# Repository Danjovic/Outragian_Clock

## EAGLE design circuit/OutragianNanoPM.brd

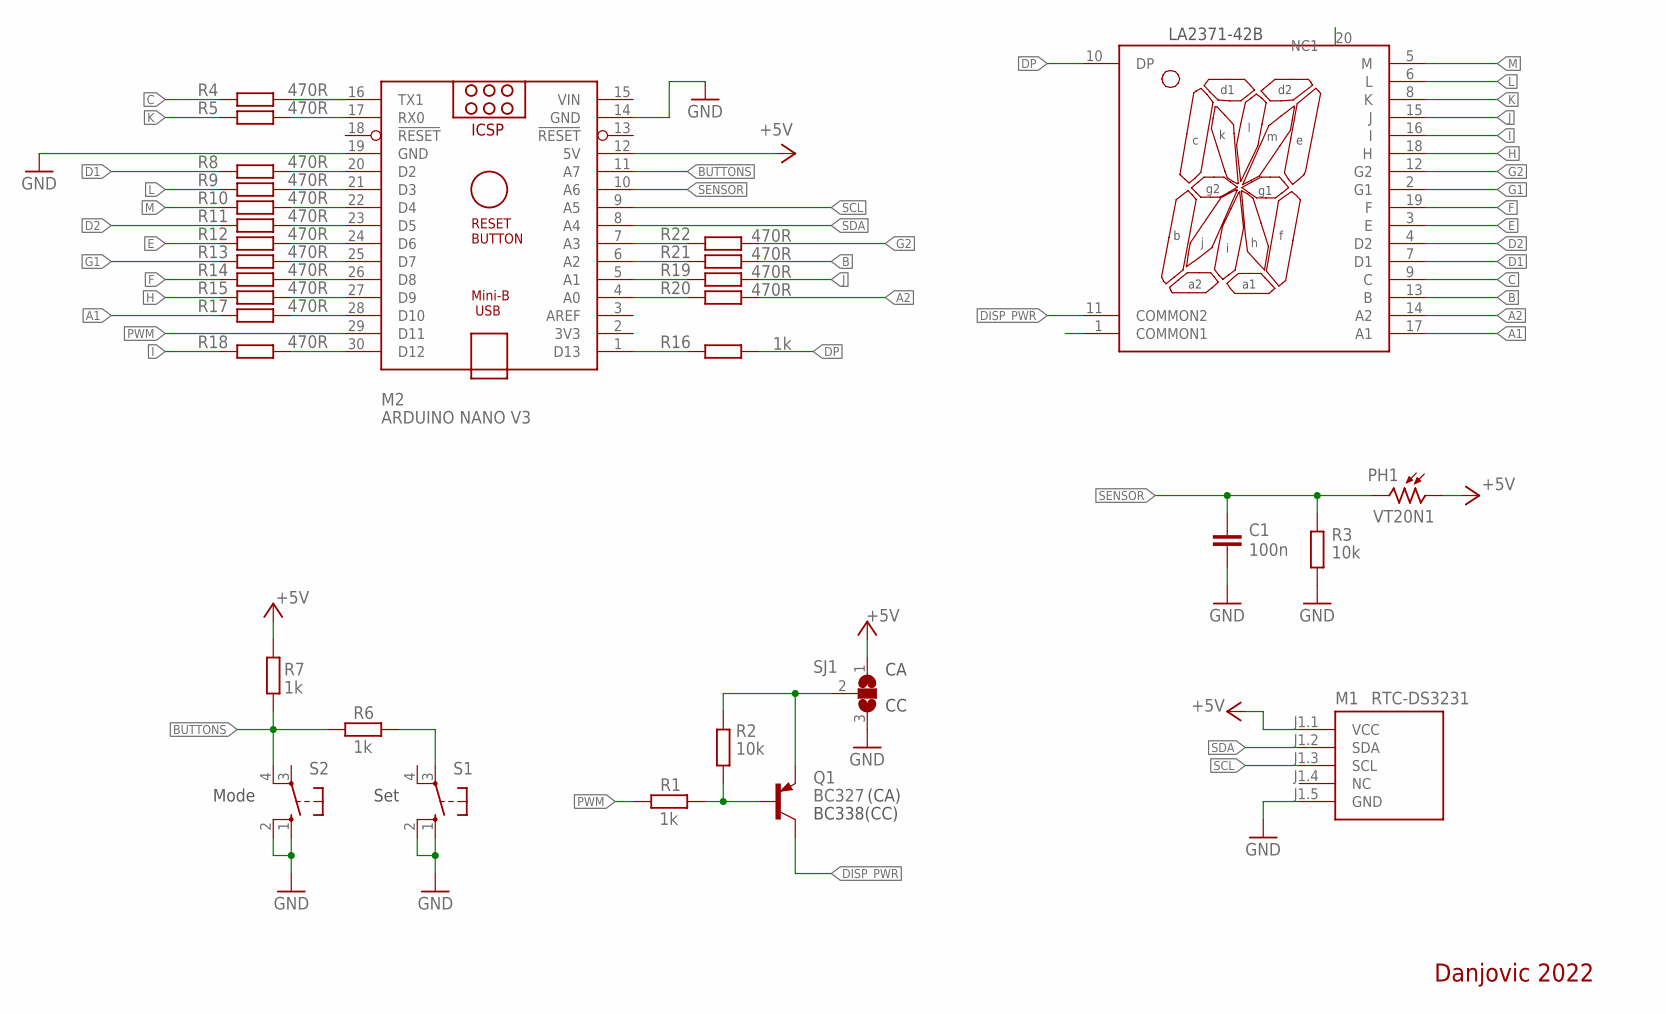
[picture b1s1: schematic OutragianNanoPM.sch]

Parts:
C1: 100n; C050-024X044L
DS1: LA2371-42B; LA(C)2371-42B-M1
M1: RTC-DS3231; RTC-DS3231_SMALL
M2: ARDUINO NANO V3; ARDUINO_NANO
PH1: VT20N1; TO46-VT200
Q1: BC327; TO92-EBC
R1, R6, R7, R16: 1k; 0204/7L
R2, R3: 10k; 0204/7L
R4, R5, R8, R9, R10, R11, R12, R13, R14, R15, R17, R18, R19, R20, R21, R22: 470R; 0204/7L
S1, S2: 10-XX; B3F-10XX
SJ1: SJ2W; SJ_2

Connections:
+5V: M1.J1.1 (VCC), M2.12 (5V), PH1.1, R7.1, SJ1.1
A1: DS1.17 (A1), R17.2
A2: DS1.14 (A2), R20.2
B: DS1.13 (B), R21.2
BUTTONS: M2.11 (A7), R6.2, R7.2, S2.4 (P1)
C: DS1.9 (C), R4.1
D1: DS1.7 (D1), R8.1
D2: DS1.4 (D2), R11.1
DDP: M2.1 (D13), R16.1
DISP_PWR: DS1.11 (COMMON2), Q1.C
DISP_PWR2: DS1.1 (COMMON1)
DP: DS1.10 (DP), DS1.20 (NC1), R16.2
E: DS1.3 (E), R12.1
F: DS1.19 (F), R14.2
G1: DS1.2 (G1), R13.1
G2: DS1.12 (G2), R22.2
GND: C1.2, M1.J1.5 (GND), M2.14 (GND), M2.19 (GND), R3.1, S1.1 (S), S1.2 (S1), S2.1 (S), S2.2 (S1), SJ1.3
H: DS1.18 (H), R15.2
I: DS1.16 (I), R18.2
J: DS1.15 (J), R19.2
K: DS1.8 (K), R5.1
L: DS1.6 (L), R9.1
M: DS1.5 (M), R10.1
unnamed: Q1.B, R1.2, R2.2
unnamed: M2.7 (A3), R22.1
unnamed: R6.1, S1.3
unnamed: M2.26 (D8), R14.1
unnamed: M2.6 (A2), R21.1
unnamed: Q1.E, R2.1, SJ1.2
unnamed: M2.5 (A1), R19.1
unnamed: M2.4 (A0), R20.1
unnamed: M2.27 (D9), R15.1
unnamed: M2.28 (D10), R17.1
unnamed: M2.30 (D12), R18.1
unnamed: M2.25 (D7), R13.2
unnamed: M2.24 (D6), R12.2
unnamed: M2.23 (D5), R11.2
unnamed: M2.22 (D4), R10.2
unnamed: M2.21 (D3), R9.2
unnamed: M2.20 (D2), R8.2
unnamed: M2.17 (RX0), R5.2
unnamed: M2.16 (TX1), R4.2
PWM: M2.29 (D11), R1.1
SCL: M1.J1.3 (SCL), M2.9 (A5)
SDA: M1.J1.2 (SDA), M2.8 (A4)
SENSOR: C1.1, M2.10 (A6), PH1.2, R3.2
VIN: M2.15 (VIN)

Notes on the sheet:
Mode
Set
LA2371-42B
Danjovic 2022
(CA)
BC338(CC)

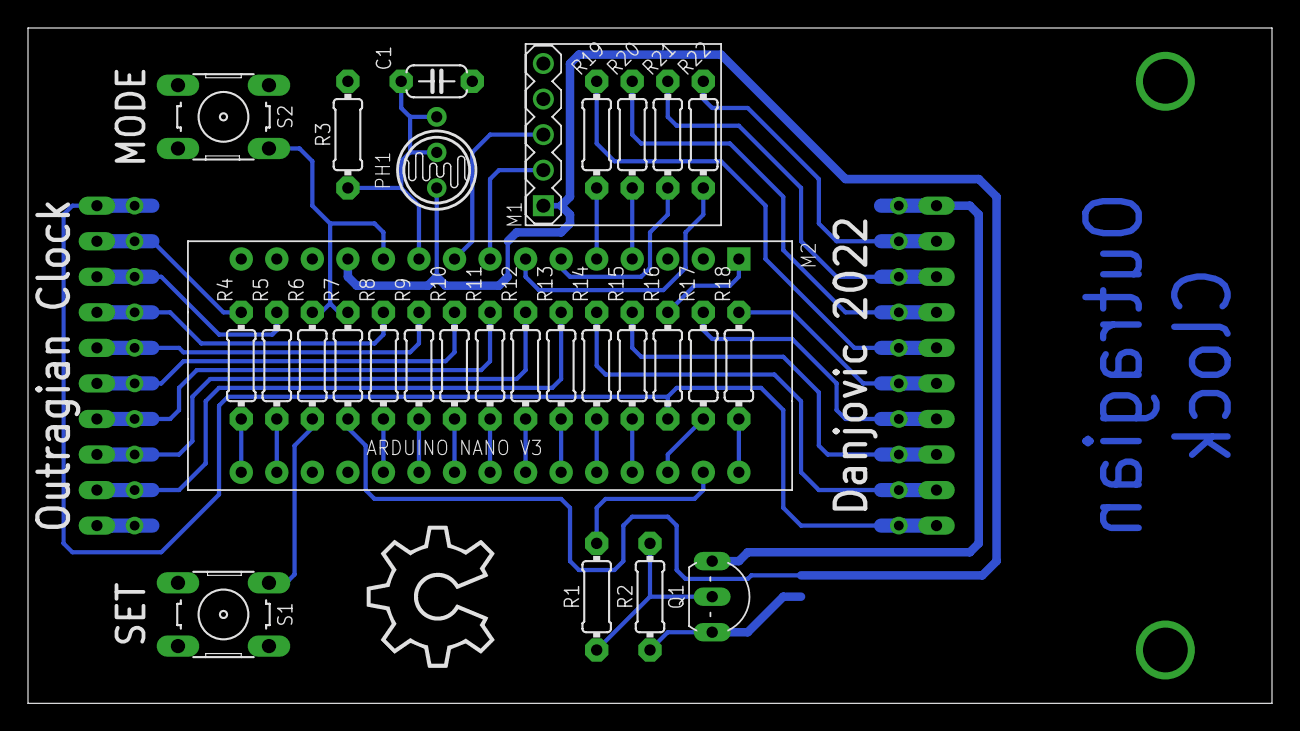
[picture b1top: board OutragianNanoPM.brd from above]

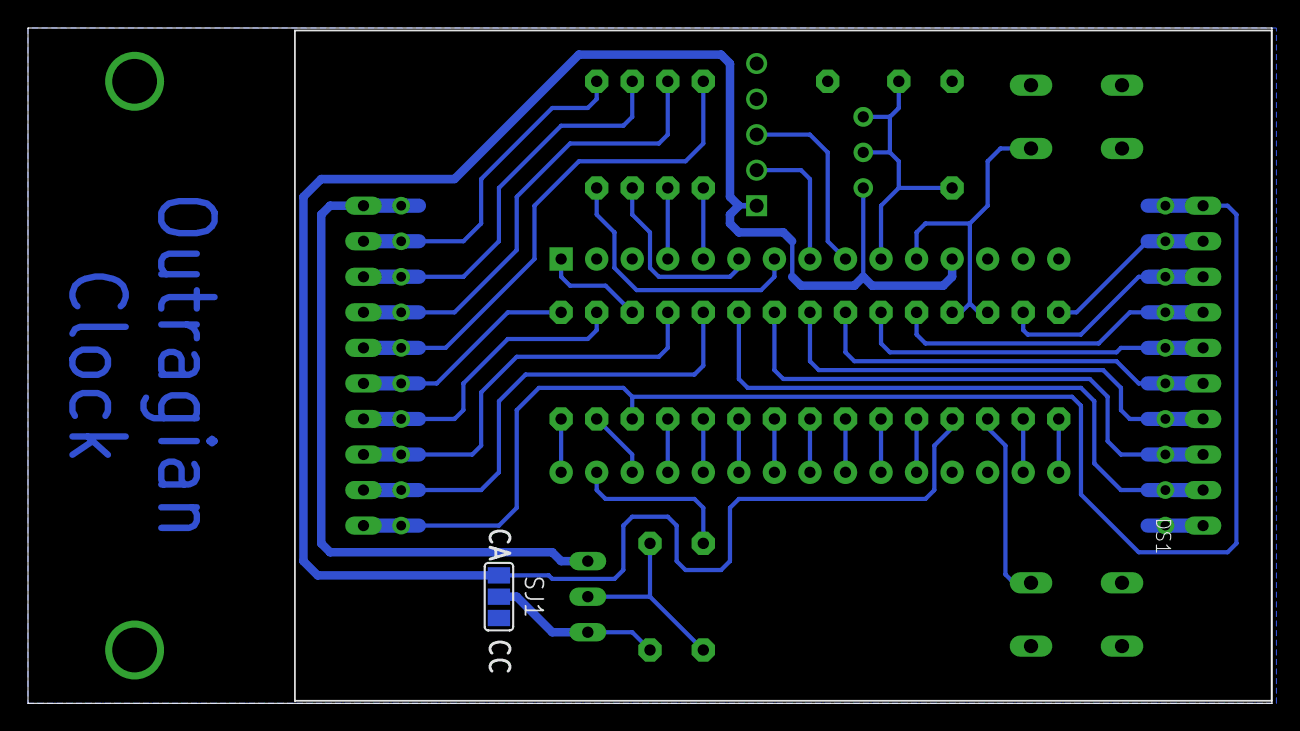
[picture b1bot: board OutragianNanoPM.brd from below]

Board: 2 copper layers, 88.9 x 48.3 mm, 31 parts (2 on the bottom side), 45 nets.
